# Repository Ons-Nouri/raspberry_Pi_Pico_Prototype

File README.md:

# raspberry_Pi_Pico_Prototype
Custom Raspberry Pi Pico-style development board designed in KiCad, featuring the RP2040/RP2350 microcontroller, USB connectivity, power management, GPIO headers, and custom PCB layout. The project covers schematic design, component selection, PCB layout, routing, and hardware validation.

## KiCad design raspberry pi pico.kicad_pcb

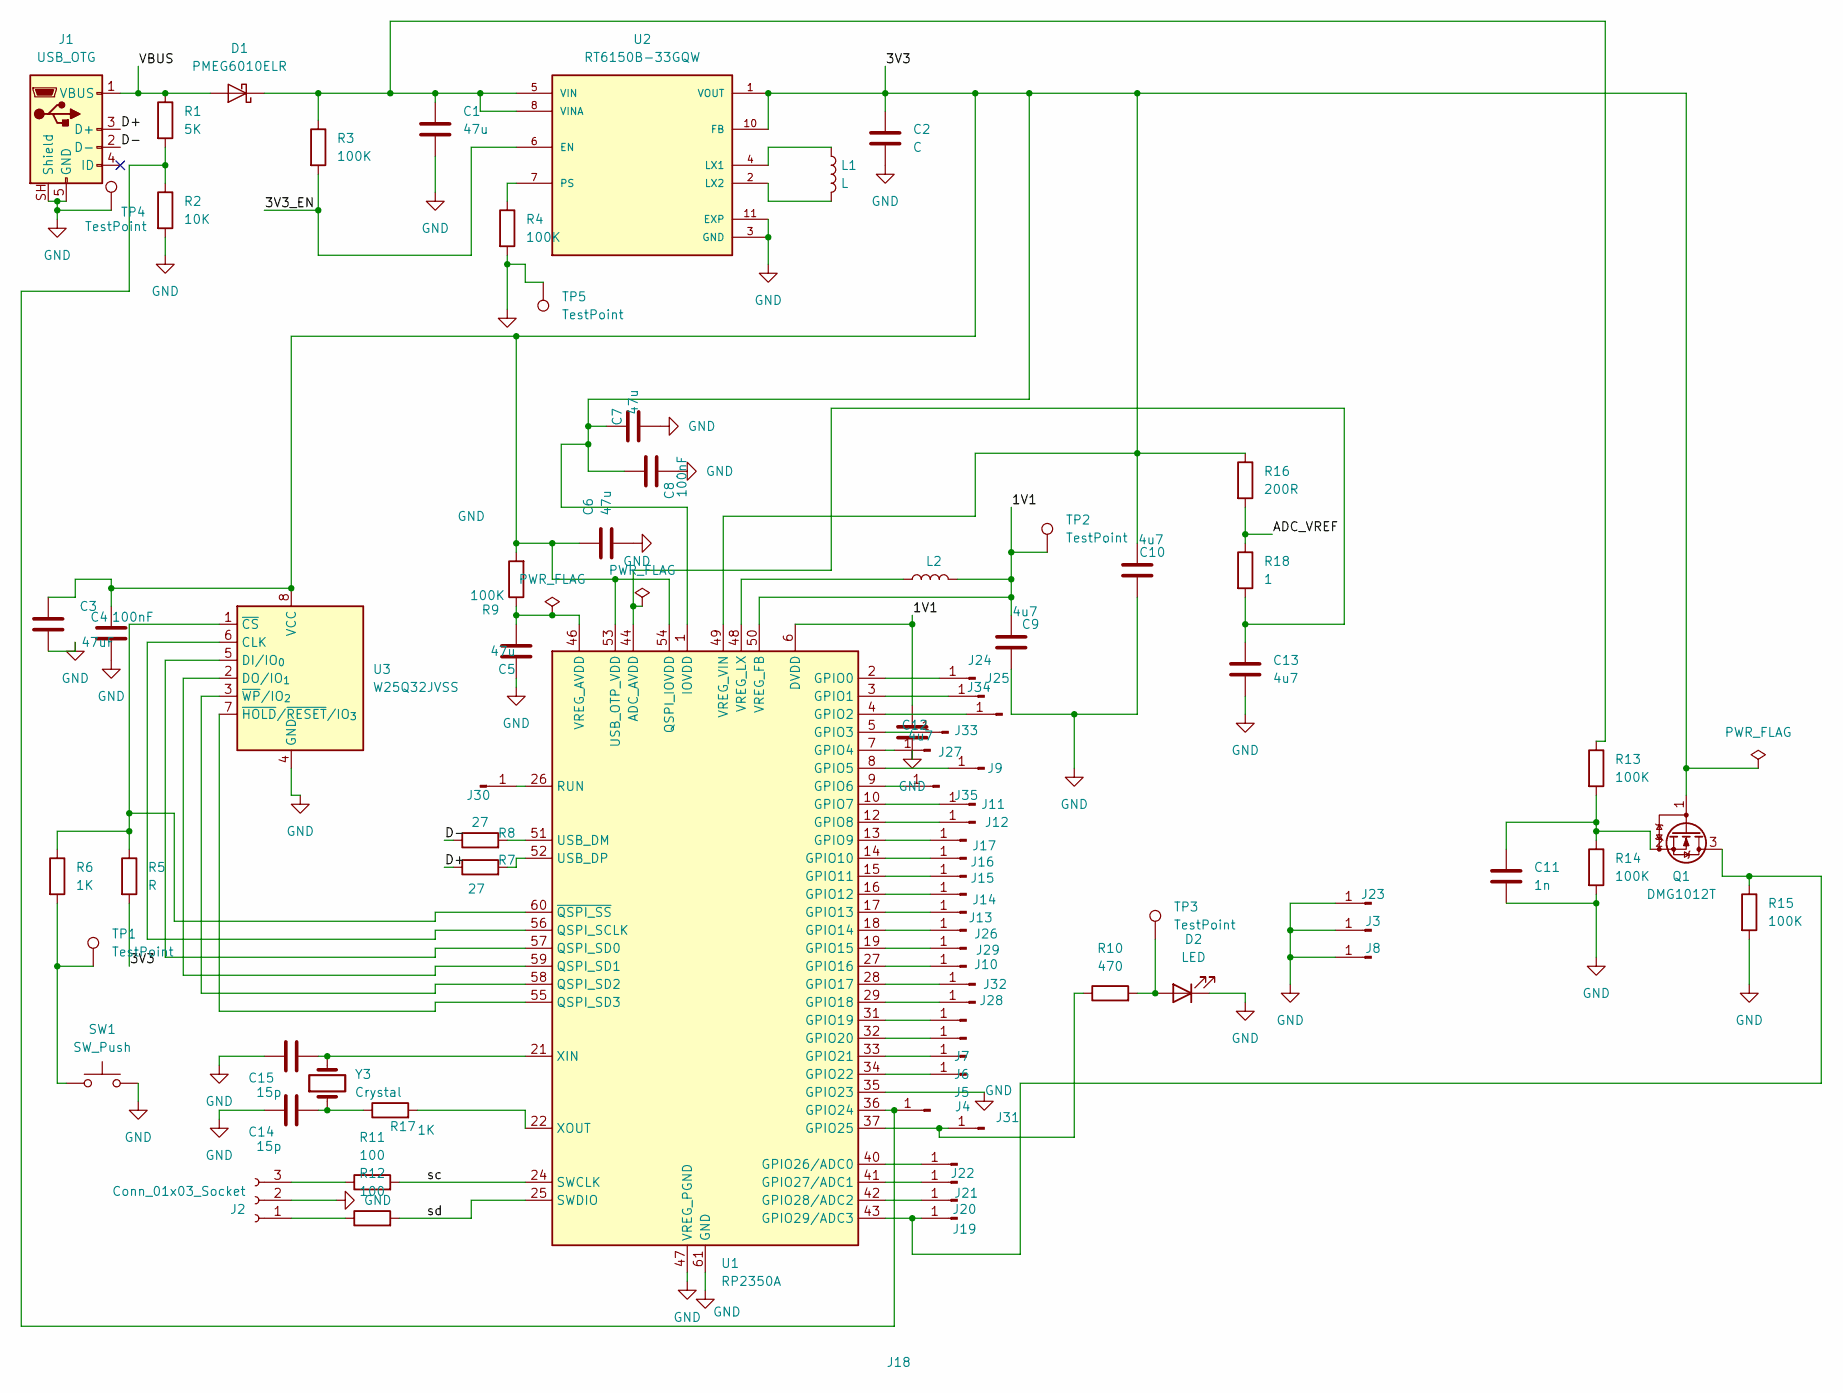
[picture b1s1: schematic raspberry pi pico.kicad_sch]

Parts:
C1, C5, C6, C7: 47u; C_0805_2012Metric_Pad1.18x1.45mm_HandSolder
C2: C; C_0805_2012Metric_Pad1.18x1.45mm_HandSolder
C3: 47uF; C_0805_2012Metric_Pad1.18x1.45mm_HandSolder
C4, C8: 100nF; C_0805_2012Metric_Pad1.18x1.45mm_HandSolder
C9, C10, C12, C13: 4u7; C_0805_2012Metric_Pad1.18x1.45mm_HandSolder
C11: 1n; C_0805_2012Metric_Pad1.18x1.45mm_HandSolder
C14, C15: 15p; C_0805_2012Metric_Pad1.18x1.45mm_HandSolder
D1: PMEG6010ELR; Nexperia_CFP3_SOD-123W
D2: LED; LED_D3.0mm
J1: USB_OTG; USB_Micro-B_Amphenol_10118194_Horizontal
J2: Conn_01x03_Socket; PinHeader_1x03_P1.00mm_Horizontal
J3, J4, J5, J6, J7, J8, J9, J10, J11, J12, J13, J14, J15, J16, J17, J18, J19, J20, J21, J22, J23, J24, J25, J26, J27, J28, J29, J30, J31, J32, J33, J34, J35: Conn_01x01_Pin; PinHeader_1x01_P1.00mm_Vertical
L1: L; L_01005_0402Metric
L2: 3u3; L_01005_0402Metric
Q1: DMG1012T; SOT-523
R1: 5K; R_0603_1608Metric_Pad0.98x0.95mm_HandSolder
R2: 10K; R_0603_1608Metric_Pad0.98x0.95mm_HandSolder
R3, R4, R9, R13, R14, R15: 100K; R_0603_1608Metric_Pad0.98x0.95mm_HandSolder
R5: R; R_0603_1608Metric_Pad0.98x0.95mm_HandSolder
R6, R17: 1K; R_0603_1608Metric_Pad0.98x0.95mm_HandSolder
R7, R8: 27; R_0603_1608Metric_Pad0.98x0.95mm_HandSolder
R10: 470; R_0603_1608Metric_Pad0.98x0.95mm_HandSolder
R11, R12: 100; R_0603_1608Metric_Pad0.98x0.95mm_HandSolder
R16: 200R; R_0603_1608Metric_Pad0.98x0.95mm_HandSolder
R18: 1; R_0603_1608Metric_Pad0.98x0.95mm_HandSolder
SW1: SW_Push; SW_PUSH_6mm
TP1, TP2, TP3, TP4, TP5: TestPoint; TestPoint_Bridge_Pitch2.54mm_Drill1.0mm
U1: RP2350A; QFN-60-1EP_7x7mm_P0.4mm_EP3.4x3.4mm
U2: RT6150B-33GQW; SON50P250X250X80-11N; PARTREV July 2018
U3: W25Q32JVSS; SOIC-8_5.3x5.3mm_P1.27mm
Y3: Crystal; Crystal_AT310_D3.0mm_L10.0mm_Horizontal

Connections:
/1V1: C9.2, C12.2, L2.2, TP2.1 (1_1), U1.6 (DVDD), U1.23 (DVDD), U1.39 (DVDD), U1.50 (VREG_FB)
/3V3: C2.1, C3.1, C4.1, C6.1, C7.1, C8.1, C10.2, Q1.1 (G), R5.2, R9.2, R16.1, U1.1 (IOVDD), U1.11 (IOVDD), U1.20 (IOVDD), U1.30 (IOVDD), U1.38 (IOVDD), U1.45 (IOVDD), U1.49 (VREG_VIN), U1.53 (USB_OTP_VDD), U1.54 (QSPI_IOVDD), U2.1 (VOUT), U2.10 (FB), U3.8 (VCC)
/3V3_EN: R3.2, U2.6 (EN)
/ADC_VREF: R16.2, R18.1
/D+: J1.3 (D+), R7.1
/D-: J1.2 (D-), R8.1
/VBUS: D1.2 (A), J1.1 (VBUS), R1.1
/sc: R11.2, U1.24 (SWCLK)
/sd: R12.2, U1.25 (SWDIO)
GND: C1.2, C2.2, C3.2, C4.2, C5.1, C6.2, C7.2, C8.2, C9.1, C10.1, C11.2, C12.1, C13.2, C14.1, C15.1, D2.1 (K), J1.5 (GND), J1.SH (Shield), J2.2, J3.1 (Pin_1_1), J8.1 (Pin_1_1), J23.1 (Pin_1_1), R2.2, R4.2, R14.2, R15.2, SW1.2, TP4.1 (1_1), TP5.1 (1_1), U1.35 (GPIO23), U1.47 (VREG_PGND), U1.61 (GND), U2.3 (GND), U2.9 (GND), U2.11 (EXP), U3.4 (GND)
unnamed: C14.2, R17.1, Y3.1
unnamed: C1.1, D1.1 (K), R3.1, R13.1, U2.5 (VIN), U2.8 (VINA)
unnamed: D2.2 (A), R10.2, TP3.1 (1_1)
unnamed: J2.1, R12.1
unnamed: J2.3, R11.1
unnamed: J4.1 (Pin_1_1), U1.34 (GPIO22)
unnamed: J5.1 (Pin_1_1), U1.33 (GPIO21)
unnamed: J6.1 (Pin_1_1), U1.32 (GPIO20)
unnamed: J7.1 (Pin_1_1), U1.31 (GPIO19)
unnamed: J9.1 (Pin_1_1), U1.8 (GPIO5)
unnamed: J10.1 (Pin_1_1), U1.27 (GPIO16)
unnamed: J11.1 (Pin_1_1), U1.10 (GPIO7)
unnamed: J12.1 (Pin_1_1), U1.12 (GPIO8)
unnamed: J13.1 (Pin_1_1), U1.17 (GPIO13)
unnamed: J14.1 (Pin_1_1), U1.16 (GPIO12)
unnamed: J15.1 (Pin_1_1), U1.15 (GPIO11)
unnamed: J16.1 (Pin_1_1), U1.14 (GPIO10)
unnamed: J17.1 (Pin_1_1), U1.13 (GPIO9)
unnamed: J18.1 (Pin_1_1), R1.2, R2.1, U1.36 (GPIO24)
unnamed: J19.1 (Pin_1_1), Q1.3 (D), R15.1, U1.43 (GPIO29/ADC3)
unnamed: J20.1 (Pin_1_1), U1.42 (GPIO28/ADC2)
unnamed: J21.1 (Pin_1_1), U1.41 (GPIO27/ADC1)
unnamed: J22.1 (Pin_1_1), U1.40 (GPIO26/ADC0)
unnamed: J24.1 (Pin_1_1), U1.3 (GPIO1)
unnamed: J25.1 (Pin_1_1), U1.4 (GPIO2)
unnamed: J26.1 (Pin_1_1), U1.18 (GPIO14)
unnamed: J27.1 (Pin_1_1), U1.7 (GPIO4)
unnamed: J28.1 (Pin_1_1), U1.29 (GPIO18)
unnamed: J29.1 (Pin_1_1), U1.19 (GPIO15)
unnamed: J30.1 (Pin_1_1), U1.26 (RUN)
unnamed: J31.1 (Pin_1_1), R10.1, U1.37 (GPIO25)
unnamed: J32.1 (Pin_1_1), U1.28 (GPIO17)
unnamed: J33.1 (Pin_1_1), U1.5 (GPIO3)
unnamed: J34.1 (Pin_1_1), U1.2 (GPIO0)
unnamed: J35.1 (Pin_1_1), U1.9 (GPIO6)
unnamed: C11.1, Q1.2 (S), R13.2, R14.1
unnamed: R6.2, SW1.1, TP1.1 (1_1)
unnamed: C13.1, R18.2, U1.44 (ADC_AVDD)
unnamed: U1.56 (QSPI_SCLK), U3.6 (CLK)
unnamed: U1.57 (QSPI_SD0), U3.5 (DI/IO_{0})
unnamed: U1.59 (QSPI_SD1), U3.2 (DO/IO_{1})
unnamed: U1.58 (QSPI_SD2), U3.3 (~WP/IO_{2})
unnamed: U1.55 (QSPI_SD3), U3.7 (~HOLD/~RESET/IO_{3})
unnamed: R8.2, U1.51 (USB_DM)
unnamed: R7.2, U1.52 (USB_DP)
unnamed: C5.2, R9.1, U1.46 (VREG_AVDD)
unnamed: L2.1, U1.48 (VREG_LX)
unnamed: C15.2, U1.21 (XIN), Y3.2
unnamed: R17.2, U1.22 (XOUT)
unnamed: R5.1, R6.1, U1.60 (~QSPI_SS), U3.1 (~CS)
unnamed: L1.1, U2.4 (LX1)
unnamed: L1.2, U2.2 (LX2)
unnamed: R4.1, U2.7 (PS)

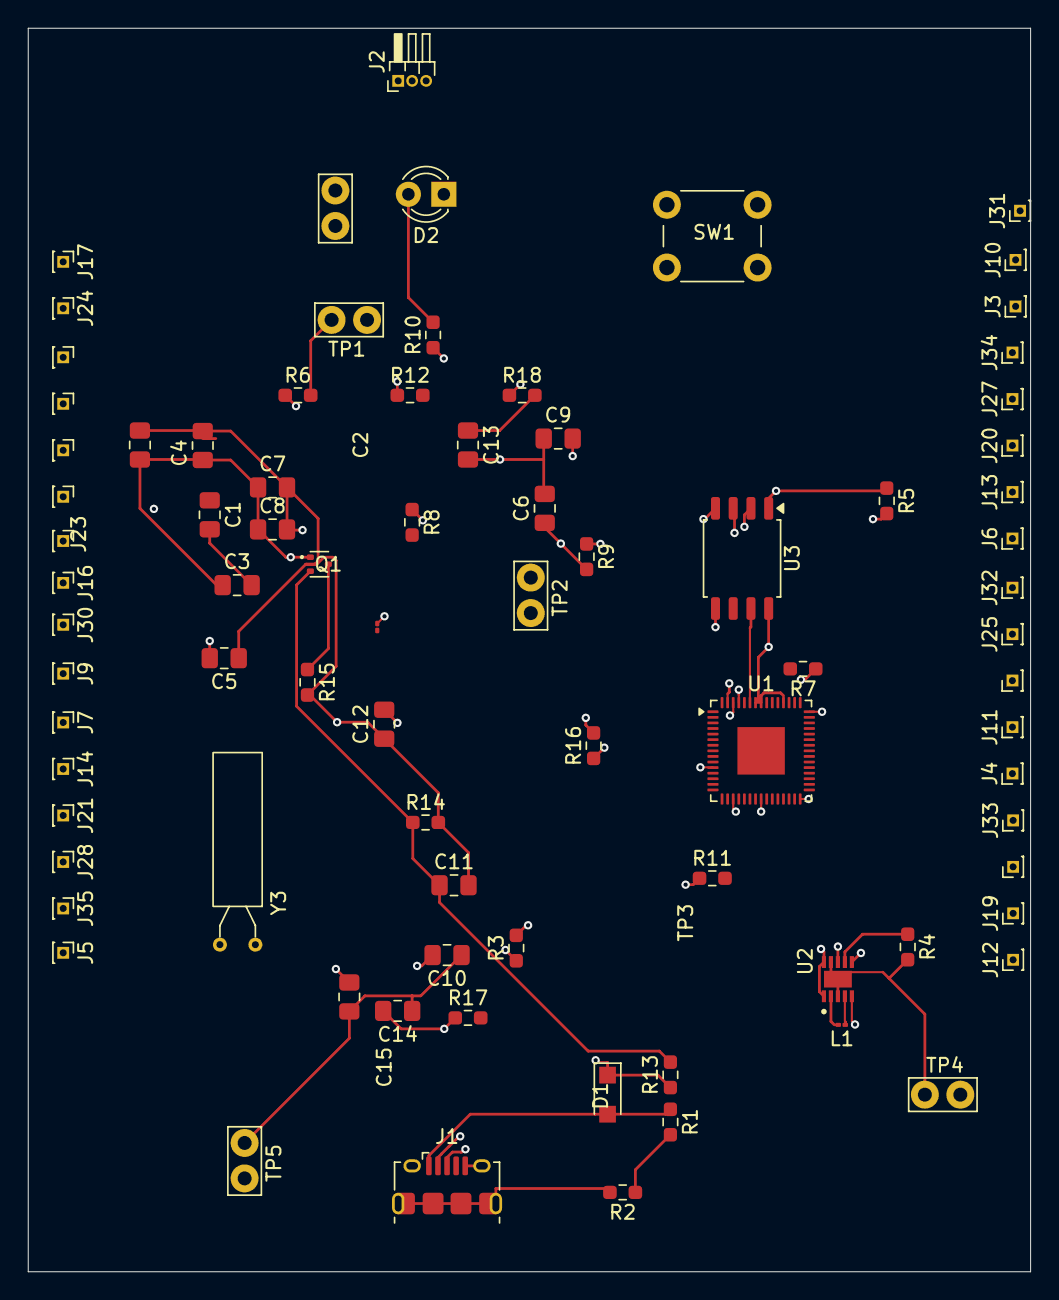
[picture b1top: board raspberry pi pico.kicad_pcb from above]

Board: 4 copper layers, 71.8 x 89.1 mm, 83 parts (0 on the bottom side), 63 nets.
